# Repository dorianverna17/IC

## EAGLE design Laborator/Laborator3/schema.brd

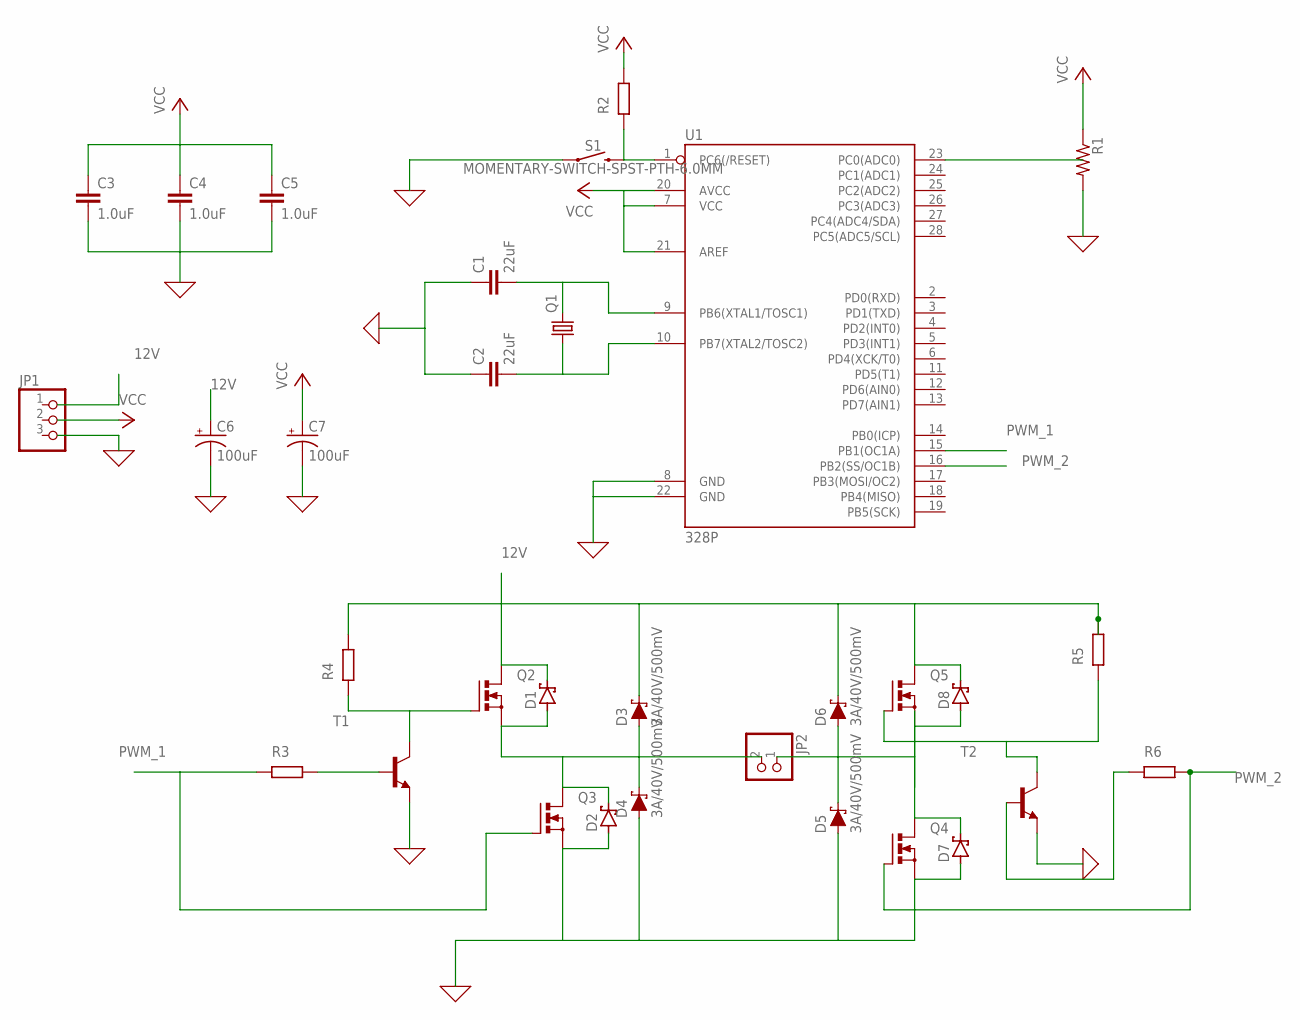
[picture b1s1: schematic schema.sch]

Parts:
C1, C2: 22uF; 0805
C3, C4, C5: 1.0uF; 0805
C6, C7: 100uF; CPOL-RADIAL-2.5MM-6.5MM
D1, D2, D7, D8: SCHOTTKY-DIODESMC; SMC
D3, D4, D5, D6: 3A/40V/500mV; SMA-DIODE
JP1: PINHD-1X3; 1X03
JP2: PINHD-1X2; 1X02
Q1: CRYSTALHC49S; HC49/S
Q2, Q3, Q4, Q5: PMOSFET_NTO220BH; TO220BH
R1: R-US_0204/2V; 0204V
S1: MOMENTARY-SWITCH-SPST-PTH-6.0MM; TACTILE_SWITCH_PTH_6.0MM
T1, T2: -NPN-SOT23-EBC; SOT23-EBC
U1: 328P; DIP28

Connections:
0: C1.1, C2.1, C3.2, C4.2, C5.2, C6.2 (-), C7.2 (-), D2.A, D4.A, D5.A, D7.A, Q3.S, Q4.S, R1.2, S1.1, T1.E, T2.E, U1.8 (GND), U1.22 (GND)
12V: C6.1 (+), D1.C, D3.C, D6.C, Q2.D
unnamed: C1.2, Q1.2, U1.9 (PB6(XTAL1/TOSC1))
unnamed: C2.2, Q1.1, U1.10 (PB7(XTAL2/TOSC2))
unnamed: S1.3 (2), U1.1 (PC6(/RESET))
unnamed: C3.1, C4.1, C5.1
unnamed: Q2.G, T1.C
unnamed: D5.C, D6.A, D7.C, JP2.1, Q4.D
unnamed: D1.A, D3.A, D4.C, JP2.2, Q2.S
unnamed: D2.C, Q3.D
unnamed: D8.A, Q5.S
unnamed: D8.C, Q5.D
unnamed: Q5.G, T2.C
PWM_1: Q3.G, U1.15 (PB1(OC1A))
PWM_2: Q4.G, U1.16 (PB2(SS/OC1B))
VCC: R1.1, U1.7 (VCC), U1.20 (AVCC), U1.21 (AREF)

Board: 2 copper layers, 27 parts (0 on the bottom side), 16 nets, no tracks yet.

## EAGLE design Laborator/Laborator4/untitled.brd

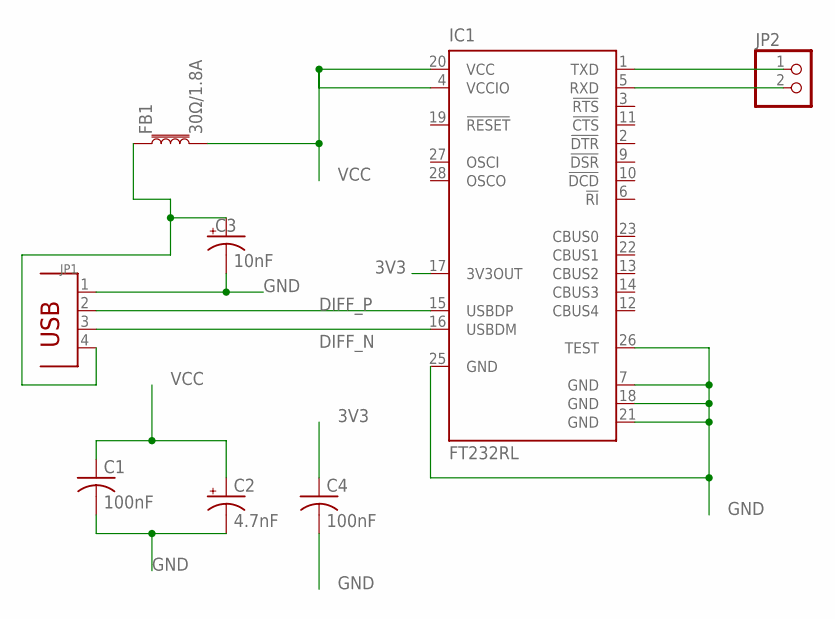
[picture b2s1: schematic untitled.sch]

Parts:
C1, C4: 100nF; C0805
C2: 4.7nF; B45181A
C3: 10nF; B45181A
FB1: 30Ω/1.8A; 0603
IC1: FT232RL; SSOP28
JP1: DIP-USB-A-TYPE-FMAL(4+2P-2.0-90D); USB4+2P-2.0-90D
JP2: PINHD-1X2; 1X02

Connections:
3V3: C4.1, IC1.17 (3V3OUT)
DIFF_N: IC1.16 (USBDM), JP1.3
DIFF_P: IC1.15 (USBDP), JP1.2
GND: C1.2, C2.-, C3.-, C4.2, IC1.7 (GND), IC1.18 (GND), IC1.21 (GND), IC1.25 (GND), IC1.26 (TEST), JP1.1
unnamed: IC1.1 (TXD), JP2.1
unnamed: IC1.5 (RXD), JP2.2
unnamed: C3.+, FB1.1, JP1.4
VCC: C1.1, C2.+, FB1.2, IC1.4 (VCCIO), IC1.20 (VCC)

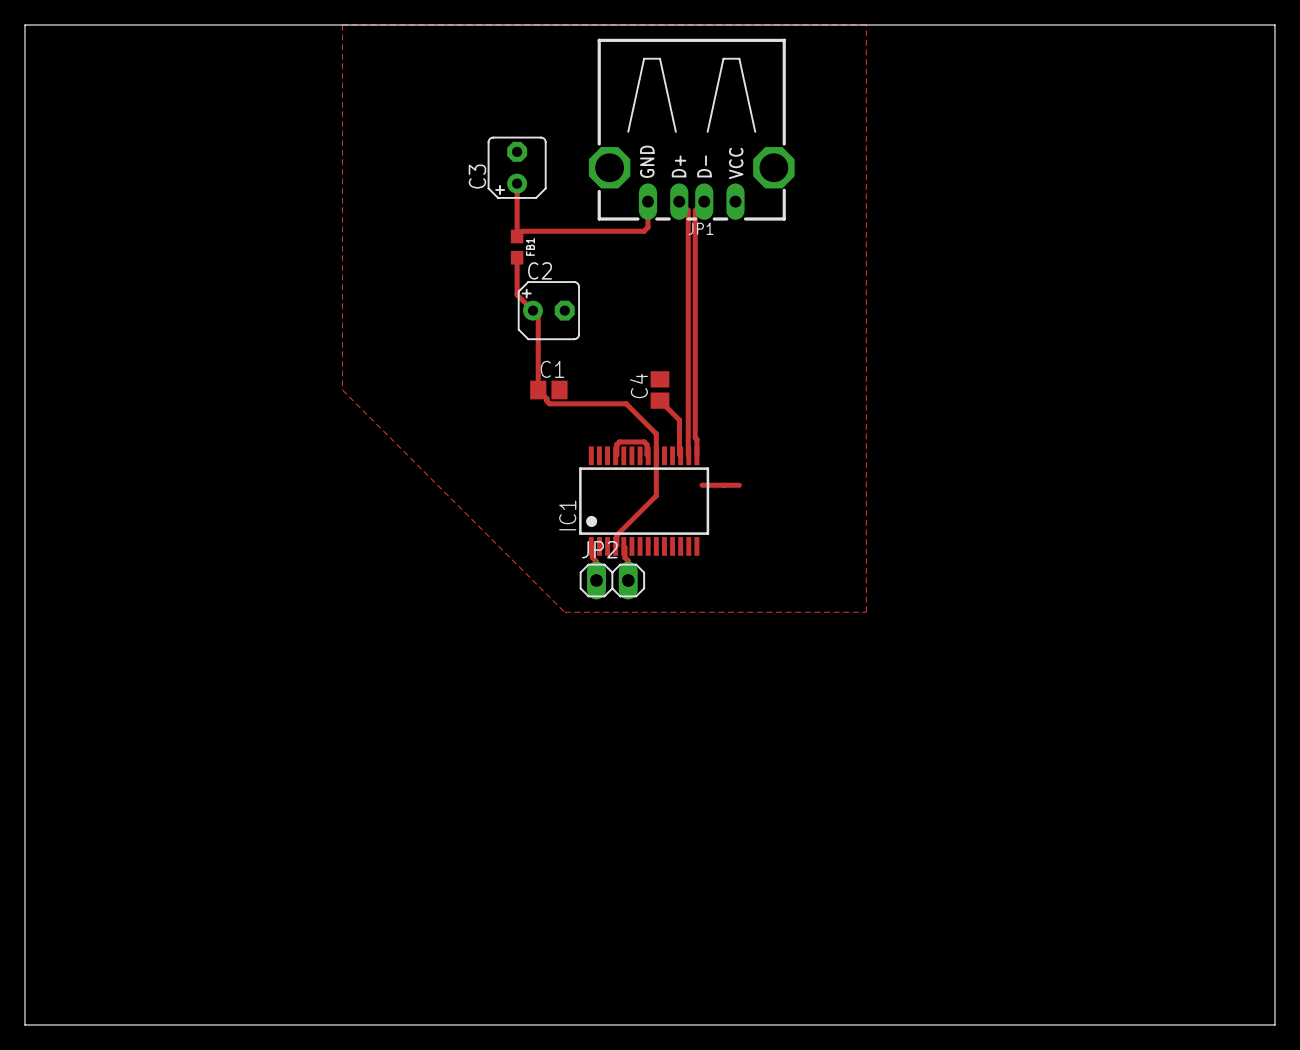
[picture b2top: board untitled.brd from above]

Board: 2 copper layers, 100.0 x 80.0 mm, 8 parts (0 on the bottom side), 8 nets.

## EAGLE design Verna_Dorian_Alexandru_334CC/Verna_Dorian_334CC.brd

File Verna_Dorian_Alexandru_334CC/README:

Verna Dorian-Alexandru 334CC
Proiect IC 2022

Pasii de implementare:
1) Intelegere schema, conexiuni, enunt tema
2) Realizare schematic
3) Realizare board
4) Asigurare ca se respecta constrangerile si regulile de
good practice (asta am aplicat-o si la pasul 3)

Realizare schematic -> am folosit biblioteca pusa la
dispozitie, din care am luat toate piesele de care am
avut nevoie (realizarea schematicului a fost partea cea
mai usoara din acest proiect).

Realizare board -> aceasta a fost partea cea mai grea.
La inceput am amplasat pisele mari conform ultimului document
atasat in enunt (pinii, reset, mode, WROVER).
Apoi am pus battery holder-ul astfel incat pad-ul sa nu fie
sub antena.
Dupa aceea am luat fiecare piesa care era in schematic si am
incercat sa o amplasez in spatiul dintre pini.
Am incercat sa iau in considerare semnalele de care are
nevoie fiecare element. De exemplu, daca o piesa are nevoie
de 3V3, atunci am incercat sa o amplasez astfel incat sa
aibe acces la 3V3 cu usurinta si sa nu blocheze alte fire,
iar firul sa nu inchida un poligon. De asemenea, am incercat
sa fac in asa fel incat sa nu am vias-uri atunci cand o sa
trag firele.
Odata ce amplasam fiecare piesa, incercam sa trag de mana firele
care faceau parte din trasee de putere: 3V3, VIN, VIN_USB, VIN_BAT.
O atentie sporita am acordat-o rutei diferentiale pe care a
trebuit sa o realizez. A fost, de altfel, unul dintre primele
lucruri pe care le-am facut la board.
Am rearanjat si rotit fiecare piesa de mai multe ori pana cand
m-am asigurat ca nu o sa am airwire-uri.
Dupa ce am tras toate firele din traseele de putere (0.3 mm),
am dat Autorouter pentru a completa cu rutele de grosime inferioara.
Surprinzator nu am avut nicio eroare, dar am avut niste warning-uri
de Wire Stub pe care le-am rezolvat destul de usor (trasesem eu putin
mai ciudat in unele locuri firele:))).

IMPORTANT: am incercat de vreo 5 sau 6 ori sa fac acest board
L-am gresit de foarte multe ori (din punctul meu de vedere) pana
cand mi-a iesit.

Apoi am facut planul de masa astfel incat sa nu cuprinda antena.
Am facut si pe BOTTOM si pe TOP si apoi am aplicat Ratsnest.

O problema pe care am avut-o a fost ca un fir de 3V3 l-am tras
ocolind antena, ceea ce era cam ciudat pentru ca nu era cuprins de
planul de masa. Asa ca am modificat board-ul astfel incat sa fie la
dreapta de antena si nu la stanga.

Am respectat dimensiunile date in schema, am folosit Dimension pentru
a masura aceste dimensiuni.

Constrangeri / Reguli de Good Practice:
-> am respecta dimensiunile necesare pentru traseele de putere
-> am aplicat verificarea cu ERC si DRC, inclusiv adaugarea fisierului
de verificare din enunt
-> Condensatoarele de decuplare le-am pus aproape de 3V3, deci de pini.
Asa cum am spus mai sus, am incercat sa amplasez piesele astfel incat
sa pot trage mai usor firele pentru semnalele de care acestea au nevoie.
-> Am incercat sa evit vias-uri la traseele de putere, VIN_BAT este pe
BOTTOM si atunci trebuia sa trec pe BOTTOM de la piesele care erau pe
TOP si foloseau acest semnal, dar din cate stiu acesta nu este
considerat un vias (pentru ca nu m-am intors pe TOP odata ce am intrat
pe BOTTOM de pe TOP). Vias-urile pe care le am sunt pe traseele simple,
care au fost generate la Autoroute.
-> Pentru ruta diferentiala, am incercat sa o fac cat mai scurta, iar
firele sa fie cat mai paralele (exceptand zonele cand se realizeaza
conexiunile)
-> Am folosit 0.3 mm pentru traseele de alimentare
-> Am incercat sa amplasez componentele conform specificatiei
-> De asemenea, am incercat sa nu am unghiuri drepte pentru trasee

In cele de ma sus consider ca am acoperit in general ceea ce trebuia
prezentat in README, nu cred ca am ratat ceva de implementat in enuntul
temei, sper sa fie ok.

Tema a fost ok, desi la inceput nu prea stiam ce vrea borad-ul de la
viata mea. A fost putin cam ciudat sa vad toate firele incurcate acolo,
dar e destul de satisfying cand la sfarsit le vezi pe toate conectate:))

Felicitari pt tema si keep up the good work!

Verna Dorian-Alexandru 334CC

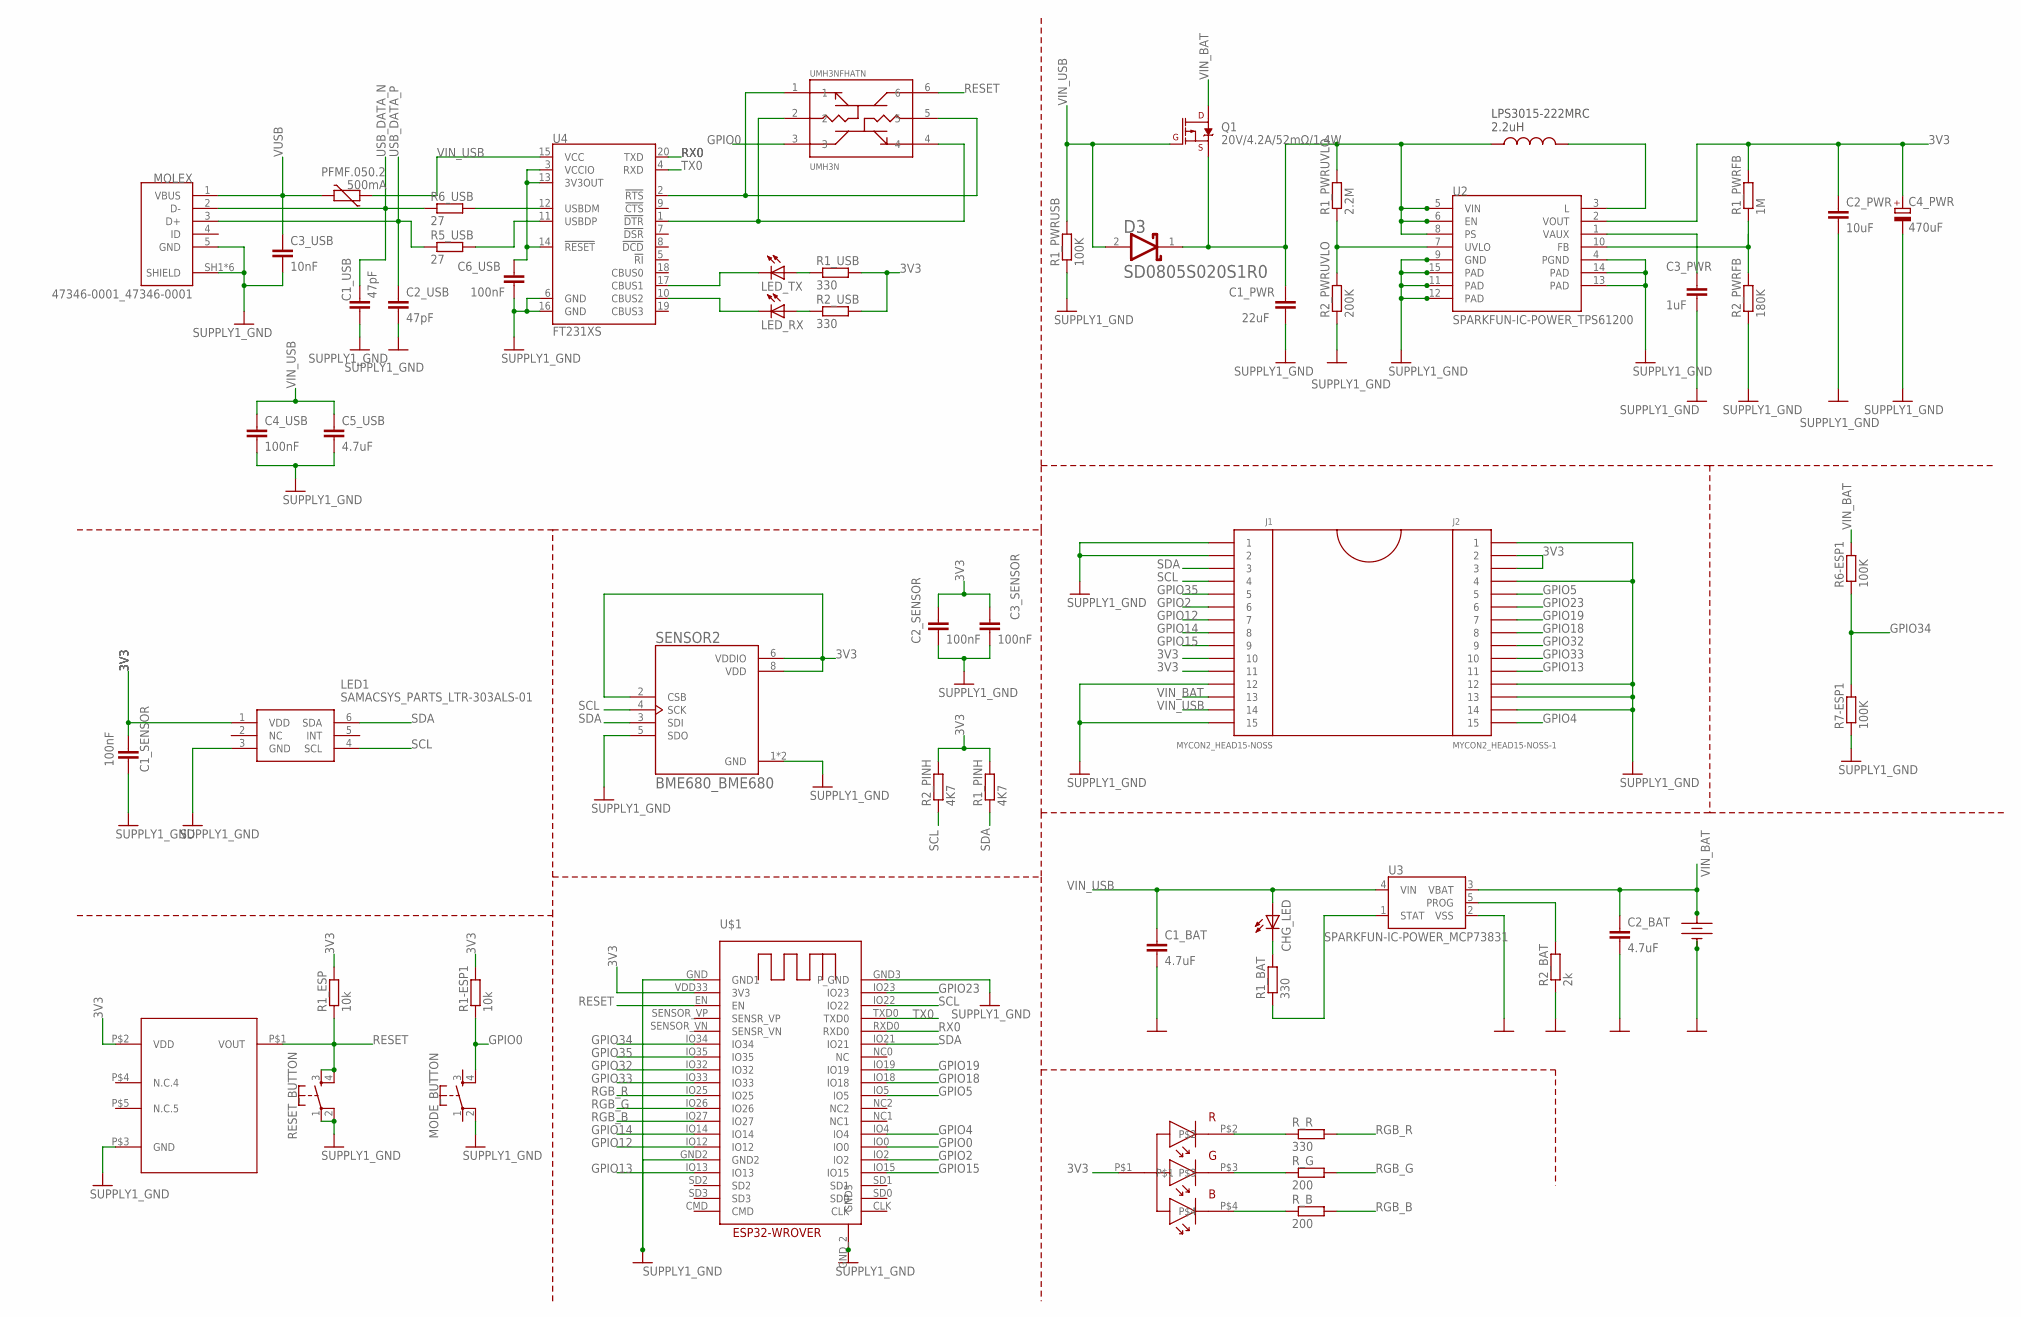
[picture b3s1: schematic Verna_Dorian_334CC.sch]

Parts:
18650BATTHOLDER: 12BHC186CLP-GR_12BHC186CLP-GR
C1_BAT, C2_BAT, C5_USB: 4.7uF; EAGLE-LTSPICE_C0402
C1_PWR: 22uF; EAGLE-LTSPICE_C0402
C1_SENSOR, C2_SENSOR, C3_SENSOR, C4_USB, C6_USB: 100nF; EAGLE-LTSPICE_C0402
C1_USB, C2_USB: 47pF; EAGLE-LTSPICE_C0402
C2_PWR: 10uF; EAGLE-LTSPICE_C0402
C3_PWR: 1uF; EAGLE-LTSPICE_C0402
C3_USB: 10nF; EAGLE-LTSPICE_C0402
C4_PWR: 470uF; RCL_D/7343-31R
CHG_LED: ADAFRUIT_LEDCHIP-LED0603; ADAFRUIT_CHIP-LED0603
D3: AVX---SD0805S020S1R0_AVX_SD0805S020S1R0AVX_SD0805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; AVX---SD0805S020S1R0_AVX_SD0805S020S1R0_0
J1: MYCON2_HEAD15-NOSS
J2: MYCON2_HEAD15-NOSS-1
LED1: SAMACSYS_PARTS_LTR-303ALS-01; SAMACSYS_PARTS_LTR303ALS01
LED_RX: ADAFRUIT_LEDCHIP-LED0603; ADAFRUIT_CHIP-LED0603
LED_TX: ADAFRUIT_LEDCHIP-LED0603; ADAFRUIT_CHIP-LED0603
MODE_BUTTON: SPARKFUN-SWITCHES_MOMENTARY-SWITCH-SPST-2-SMD-4.6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; SPARKFUN-SWITCHES_TACTILE_SWITCH_SMD_4.6X2.8MM
MOLEX: 47346-0001_47346-0001; 47346-0001_MOLEX_47346-0001
PFMF.050.2: 500mA; VARISTOR_CT/CN1812
Q1: 20V/4.2A/52mΩ/1.4W; SPARKFUN-DISCRETESEMI_SOT23-3
R1-ESP1, R1_ESP: 10k; EAGLE-LTSPICE_R0402
R1_BAT, R1_USB, R2_USB: 330; EAGLE-LTSPICE_R0402
R1_PINH, R2_PINH: 4K7; EAGLE-LTSPICE_R0402
R1_PWRFB: 1M; EAGLE-LTSPICE_R0402
R1_PWRUSB, R6-ESP1, R7-ESP1: 100K; EAGLE-LTSPICE_R0402
R1_PWRUVLO: 2.2M; EAGLE-LTSPICE_R0402
R2_BAT: 2k; EAGLE-LTSPICE_R0402
R2_PWRFB: 180K; EAGLE-LTSPICE_R0402
R2_PWRUVLO: 200K; EAGLE-LTSPICE_R0402
R5_USB, R6_USB: 27; EAGLE-LTSPICE_R0402
RESET_BUTTON: SPARKFUN-SWITCHES_MOMENTARY-SWITCH-SPST-2-SMD-4.6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; SPARKFUN-SWITCHES_TACTILE_SWITCH_SMD_4.6X2.8MM
R_B: 200; EAGLE-LTSPICE_R0402
R_G: 200; EAGLE-LTSPICE_R0402
R_R: 330; EAGLE-LTSPICE_R0402
SENSOR2: BME680_BME680; BME680_PSON80P300X300X100-8N
U2: SPARKFUN-IC-POWER_TPS61200; SPARKFUN-IC-POWER_QFN-10_PAD
U3: SPARKFUN-IC-POWER_MCP73831; SPARKFUN-IC-POWER_SOT23-5
U4: FT231XS; SPARKFUN-IC-COMMS_SSOP20_L
U$1: ESP32-WROVER_ESP32-WROVER
U$2: 150202M153130_150202M153130-RGB; 150202M153130_150202M153130
U$3: BD48E27G-TR_BD48E27G-TR; BD48E27G-TR_SSOP5
U$6: LPS3015_LPS3015; LPS3015_LPS3015-222MRC
UMH3NFHATN: UMH3N_UMH3N; UMH3N_SOP65P210X100-6N

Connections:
3V3: C1_SENSOR.1, C2_PWR.1, C2_SENSOR.1, C3_SENSOR.1, C4_PWR.+, J1.10, J1.11, J2.2, J2.3, LED1.1 (VDD), R1-ESP1.2, R1_ESP.2, R1_PINH.2, R1_PWRFB.2, R1_USB.2, R2_PINH.2, R2_USB.2, SENSOR2.2 (CSB), SENSOR2.6 (VDDIO), SENSOR2.8 (VDD), U2.2 (VOUT), U$1.VDD33 (3V3), U$2.P$1, U$3.P$2 (VDD)
GND: 18650BATTHOLDER.P$1 (G), 18650BATTHOLDER.P$3 (G), 18650BATTHOLDER.P$4 (G), C1_BAT.2, C1_PWR.2, C1_SENSOR.2, C1_USB.2, C2_BAT.2, C2_PWR.2, C2_SENSOR.2, C2_USB.2, C3_PWR.2, C3_SENSOR.2, C3_USB.2, C4_PWR.-, C4_USB.2, C5_USB.2, C6_USB.2, J1.1, J1.2, J1.12, J1.15, J2.1, J2.4, J2.12, J2.13, J2.14, LED1.3 (GND), MODE_BUTTON.2, MOLEX.5 (GND), MOLEX.SH1 (SHIELD), MOLEX.SH2 (SHIELD), MOLEX.SH3 (SHIELD), MOLEX.SH4 (SHIELD), MOLEX.SH5 (SHIELD), MOLEX.SH6 (SHIELD), R1_PWRUSB.1, R2_BAT.1, R2_PWRFB.1, R2_PWRUVLO.1, R7-ESP1.1, RESET_BUTTON.1, RESET_BUTTON.2, SENSOR2.1 (GND), SENSOR2.5 (SDO), SENSOR2.7 (GND), U2.4 (PGND), U2.9 (GND), U2.11 (PAD), U2.12 (PAD), U2.13 (PAD), U2.14 (PAD), U2.15 (PAD), U3.2 (VSS), U4.6 (GND), U4.16 (GND), U$1.GND (GND1), U$1.GND2, U$1.GND3 (P_GND), U$1.GND_2 (GND3), U$3.P$3 (GND)
GPIO0: MODE_BUTTON.4, R1-ESP1.1, U$1.IO0, UMH3NFHATN.3
GPIO2: J1.6, U$1.IO2
GPIO4: J2.15, U$1.IO4
GPIO5: J2.5, U$1.IO5
GPIO12: J1.7, U$1.IO12
GPIO13: J2.11, U$1.IO13
GPIO14: J1.8, U$1.IO14
GPIO15: J1.9, U$1.IO15
GPIO18: J2.8, U$1.IO18
GPIO19: J2.7, U$1.IO19
GPIO23: J2.6, U$1.IO23
GPIO32: J2.9, U$1.IO32
GPIO33: J2.10, U$1.IO33
GPIO34: R6-ESP1.1, R7-ESP1.2, U$1.IO34
GPIO35: J1.5, U$1.IO35
unnamed: R_R.1, U$2.P$2
unnamed: R_G.1, U$2.P$3
unnamed: R_B.1, U$2.P$4
unnamed: U2.3 (L), U$6.P$2
unnamed: CHG_LED.C, R1_BAT.2
unnamed: R1_BAT.1, U3.1 (STAT)
unnamed: R2_BAT.2, U3.5 (PROG)
unnamed: R6_USB.2, U4.12 (USBDM)
unnamed: C3_PWR.1, U2.1 (VAUX)
unnamed: R5_USB.2, U4.11 (USBDP)
unnamed: R1_PWRUVLO.1, R2_PWRUVLO.2, U2.7 (UVLO)
unnamed: R1_PWRFB.1, R2_PWRFB.2, U2.10 (FB)
unnamed: C6_USB.1, U4.3 (VCCIO), U4.13 (3V3OUT), U4.14 (!RESET)
unnamed: LED_TX.C, U4.17 (CBUS1)
unnamed: LED_RX.C, U4.10 (CBUS2)
unnamed: LED_TX.A, R1_USB.1
unnamed: LED_RX.A, R2_USB.1
unnamed: U4.1 (!DTR), UMH3NFHATN.2, UMH3NFHATN.4
unnamed: U4.2 (!RTS), UMH3NFHATN.1, UMH3NFHATN.5
RESET: R1_ESP.1, RESET_BUTTON.3, RESET_BUTTON.4, U$1.EN, U$3.P$1 (VOUT), UMH3NFHATN.6
RGB_B: R_B.2, U$1.IO27
RGB_G: R_G.2, U$1.IO26
RGB_R: R_R.2, U$1.IO25
RX0: U4.20 (TXD), U$1.RXD0
SCL: J1.4, LED1.4 (SCL), R2_PINH.1, SENSOR2.4 (SCK), U$1.IO22
SDA: J1.3, LED1.6 (SDA), R1_PINH.1, SENSOR2.3 (SDI), U$1.IO21
TX0: U4.4 (RXD), U$1.TXD0
USB_DATA_N: C1_USB.1, MOLEX.2 (D-), R6_USB.1
USB_DATA_P: C2_USB.1, MOLEX.3 (D+), R5_USB.1
VIN: C1_PWR.1, D3.1 (CATHODE), Q1.2 (S), R1_PWRUVLO.2, U2.5 (VIN), U2.6 (EN), U2.8 (PS), U$6.P$1
VIN_BAT: 18650BATTHOLDER.P$2, 18650BATTHOLDER.P$5, 18650BATTHOLDER.P$6, C2_BAT.1, J1.13, Q1.3 (D), R6-ESP1.2, U3.3 (VBAT)
VIN_USB: C1_BAT.1, C4_USB.1, C5_USB.1, CHG_LED.A, D3.2 (ANODE), J1.14, PFMF.050.2.1, Q1.1 (G), R1_PWRUSB.2, U3.4 (VIN), U4.15 (VCC)
VUSB: C3_USB.1, MOLEX.1 (VBUS), PFMF.050.2.2

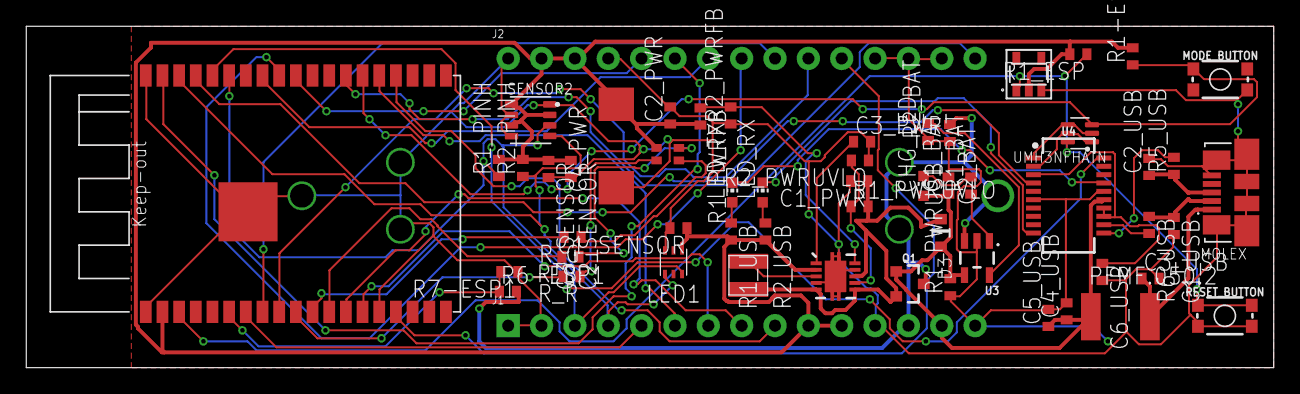
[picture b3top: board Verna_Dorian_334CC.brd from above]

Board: 2 copper layers, 95.0 x 26.0 mm, 57 parts (1 on the bottom side), 50 nets.

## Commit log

2022-04-20 added README file
2022-07-17 Added lab8

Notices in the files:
parts and their libraries:
SparkFun-Capacitors: Licensing: Creative Commons ShareAlike 4.0 International - https://creativecommons.org/licenses/by-sa/4.0
